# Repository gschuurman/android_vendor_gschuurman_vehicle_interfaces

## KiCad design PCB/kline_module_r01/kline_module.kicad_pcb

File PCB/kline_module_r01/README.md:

# K-line module rev 0.1 (MG F, MEMS 1.9) - 2026-11-15

A small 2-layer board that stacks on main board rev 0.6 socket **J10**, like the other modules, and connects the
RP2350B UART to the car's K-line through Glenn's ST **L9637D**.

- Size **28.5 x 20.5 mm**, 1.6 mm, 2 layers, GND pour on both sides. Well inside the JLCPCB 100 x 100 mm promo.
- Status: fully routed, **0 unconnected, 0 copper/clearance errors**. `drc.rpt` only lists the KiCad standard library
  names (not installed in the build container) and one silkscreen nick at a corner.
- All parts are 0805 or larger (SOT-23, SOD-123, SMA, SO-8, 2512), all on the top side. Only the 2x4 header sits underneath.
- Files: `kline_module.kicad_pro/.kicad_pcb/.kicad_sch` (made in KiCad 7, open in KiCad 10), `kline_module_gerbers.zip`
  (upload to JLCPCB), `kline_module_bom.csv`, `kline_module_lcsc_order.csv` (LCSC numbers and quantity per board),
  `kline_module_schematic.pdf`, renders in `render/`, generator scripts in `scripts/` (placement and netlist in `design.py`).

## Fit on the main board (rev 0.6)

The board is drawn in main-board coordinates, so it can be checked directly against `carradio_peripheral_rev06.kicad_pcb`.

| What | Main board | Module |
|---|---|---|
| J10 (2x4 socket, 8.5 mm) | pin 1 at (78.19, 27.63) | J1 2x4 male header on the underside, pin 1 at (78.19, 27.63); all 8 pins checked in the script |
| H8 (M2) | (69.6, 18.5) | H1 2.2 mm hole at (69.6, 18.5), copper keep-out 5.2 mm |
| outline | free zone above J10 | x 65.0-93.5, y 11.5-32.0 (audio module ends at x 63.5, USB module starts at y 32.5) |

Under the module there are only low SMD parts, the J10 socket, F6 and the HDMI pairs. The module edge reaches
0.5 mm over the back of the HDMI socket J13 (courtyard to y 12.0), which is about 6 mm tall, so there is ~5 mm of air
at the 11 mm stack height. It stays clear of the FPC J14 (starts at x 94.2); unplug the module to open the J14 latch.
Screw: M2 x 18 through the module, the printed 11 mm M2 sleeve (`module_spacers`) and the main board into the H8 insert.

J1 is two 1x4 male headers (Ckmtw B-2100S04P-A110, same family as earlier boards), one per row. Plug them into J10
first, put the module on top and solder them from above, so they line up.

## Circuit

| J1 pin | Main board net | Use |
|---|---|---|
| 1 | +3V3_MCU | U1 VCC |
| 2, 6 | GND | |
| 3 | EXP_GP32 (UART0 TX) | U1 TX |
| 4 | EXP_GP33 (UART0 RX) | U1 RX |
| 5 | EXP_GP28 | K-line power enable (high = on) |
| 7 | VBAT_KLINE (via F6, after D1 reverse diode and SMBJ22A) | Q1 source |
| 8 | +5V_AON | not used |

- **U1 L9637D**: VCC from 3.3 V is inside the datasheet range (3-7 V). RX then swings 0-3.3 V straight into GPIO33,
  and TX accepts 3.3 V logic (VIH max 2.5 V). TX, RX and LO have internal pull-ups to VCC, so nothing else is needed.
  VS max 36 V; the main-board TVS clamps at 35.5 V.
- **Q1 FDN5618P** (same as main-board Q2) with D1 12 V zener, R2 100k and Q2 2N7002 + R3: switches battery to VS and to the
  pull-up. GPIO28 low (also the default through R4 10k) = off. That gives zero parked drain and, more importantly,
  no 12 V pushed through 510 ohm into the ECU's K-line while the ECU is unpowered.
- **R1 510 ohm 2512** (1 W, 0.4 W worst case with K stuck low): the ISO 9141 tester pull-up. **JP1** is a bridged solder jumper;
  cut it if you want to run without the module's pull-up.
- **D2 SMAJ26CA** bidirectional TVS and **C4 1 nF** on K (ISO 9141 allows up to 1.3 nF; 470 pF also fine).
- **D3** green LED: lit while the K-line side is powered.
- L-line is not used by the MEMS 1.9: LI and LO stay open (the datasheet defines LO for an open LI).

## Car side

**J2 = JST S2B-XH-A side entry** (2.5 mm XH, crimp housing XHP-2), pin 1 **K-line**, pin 2 **GND**. The opening faces
the back plate (main-board x = 100). Glenn's harness already uses XH for the VIM3 power, so the same crimps work.
- Forum sources (not a wiring diagram) say the MEMS 1.9 K-line is OBD-II socket pin 7 (ECU red connector pin 31 on at
  least one car), GND pins 4/5. Check this on your car before wiring.
- Space: the plug and wire leave the module edge at x 93.3; the back plate inner face is at about x 101. That is
  tight for a bend; a small hole/grommet in the back plate lets the wire run straight out.

## Firmware notes (not written yet)

- GPIO28 high, wait ~10 ms, then talk.
- MEMS 1.9 (per rovermems.com): ISO 9141 5-baud init with ECU address 0x16, bit-banged on GPIO32 as SIO, then UART0
  **9600 8N1** half duplex (you read back your own echo on GPIO33).
- GPIO28 low when ACC goes off.

## Order

JLCPCB: upload `kline_module_gerbers.zip`, defaults (2 layers, 1.6 mm, HASL, 5 pcs), no assembly.

Parts (checked against the rev 0.6 order of 2026-10-04, `pcb/ordering/lcsc_final_cart.csv` + `mouser_final_import.csv`,
assuming one set built with at most 2 spares used):

| Ref | Part | Source |
|---|---|---|
| U1 | L9637D | Glenn's own |
| J2 | JST XH 2-pin right angle | Glenn's own; cable needs an XHP-2 housing + 2 SXH crimps |
| Q1 | FDN5618P | rev 0.6 leftover (5 ordered, 1 used) |
| D1 | BZT52C12 | leftover (10 ordered, 2 used) |
| Q2 | 2N7002 | leftover (50 ordered) |
| D3 | KT-0805G LED | leftover (50 ordered) |
| R5 | 4.7k 0805 | leftover (100 ordered) |
| C1, C2 | 100 nF | leftover 0603 C14663 (150 ordered, ~48 used); fits the 0805 pads |
| R3, R4 | 10k | leftover 0603 C98220 (40 ordered, ~18 used) |
| R2 | 100k | leftover 0603 C25803 (100 ordered) |
| C4 | 1 nF | leftover 0603 C1588 (6 ordered, 1 used) |
| J1 | 2x 1x4 header | leftover C124378 (10 ordered, 1 used) |
| **R1** | **510R 2512 1W** | **buy: LCSC C269361** |
| **D2** | **SMAJ26CA** | **buy: LCSC C571371** |

`kline_module_lcsc_order.csv` holds only the two parts to buy; `kline_module_bom.csv` is the full BOM.

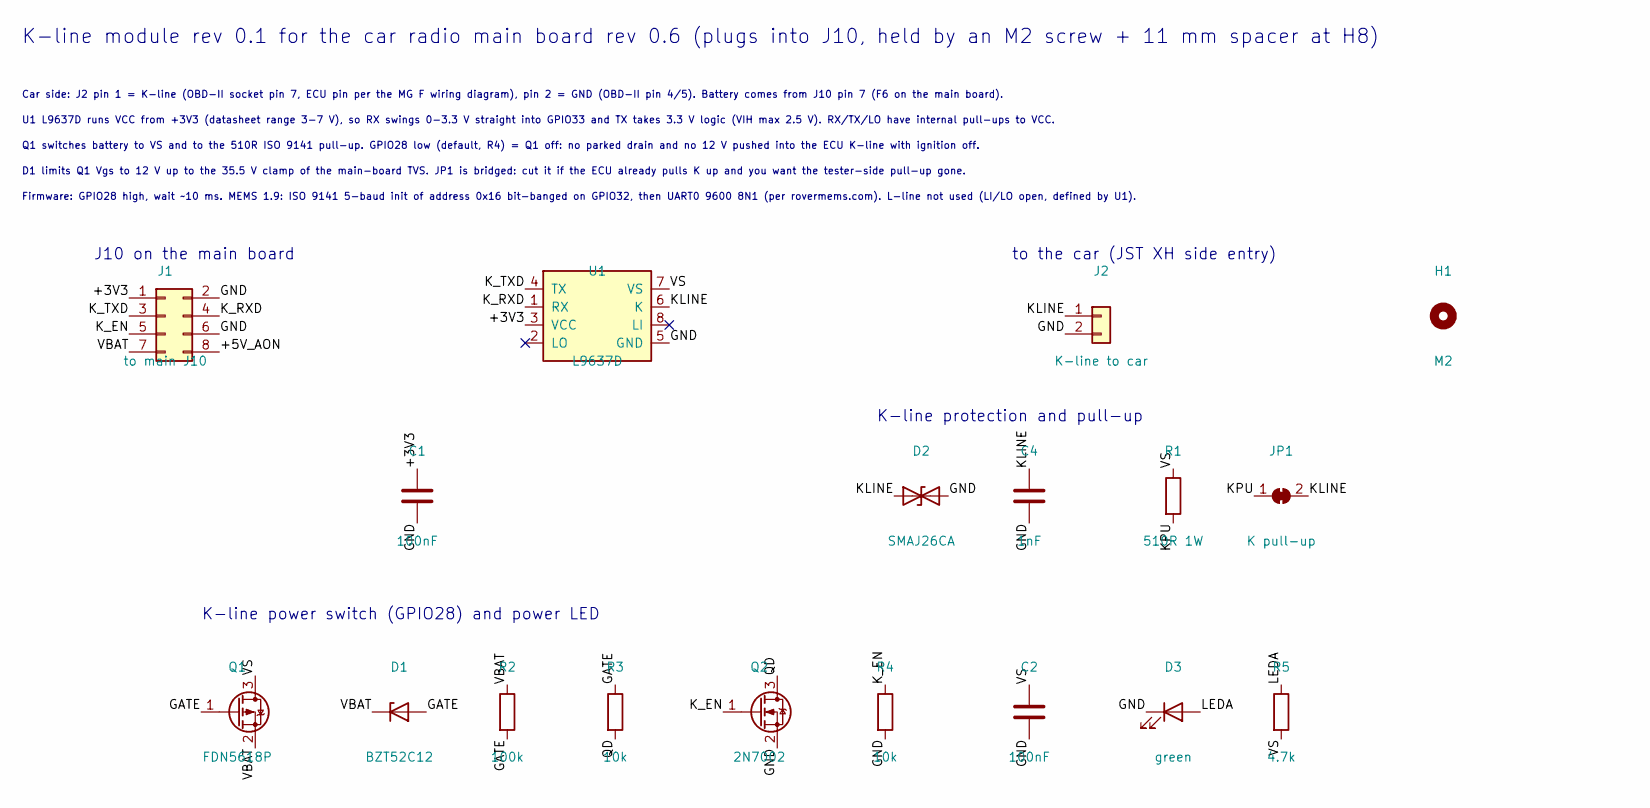
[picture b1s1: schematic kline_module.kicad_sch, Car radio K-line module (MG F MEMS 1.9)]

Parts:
C1, C2: 100nF; C_0805_2012Metric_Pad1.18x1.45mm_HandSolder; LCSC C49678
C4: 1nF; C_0805_2012Metric_Pad1.18x1.45mm_HandSolder; LCSC C1588
D1: BZT52C12; D_SOD-123; LCSC C124196
D2: SMAJ26CA; D_SMA; LCSC C571371
D3: green; LED_0805_2012Metric_Pad1.15x1.40mm_HandSolder; LCSC C2297
H1: M2; MountingHole_2.2mm_M2
J1: to main J10; PinHeader_2x04_P2.54mm_Vertical; LCSC C124378
J2: K-line to car; JST_XH_S2B-XH-A_1x02_P2.50mm_Horizontal; LCSC C157931
JP1: K pull-up; SolderJumper-2_P1.3mm_Bridged_RoundedPad1.0x1.5mm
Q1: FDN5618P; SOT-23; LCSC C400792
Q2: 2N7002; SOT-23; LCSC C8545
R1: 510R 1W; R_2512_6332Metric_Pad1.40x3.35mm_HandSolder; LCSC C269361
R2: 100k; R_0805_2012Metric_Pad1.20x1.40mm_HandSolder; LCSC C149504
R3, R4: 10k; R_0805_2012Metric_Pad1.20x1.40mm_HandSolder; LCSC C17414
R5: 4.7k; R_0805_2012Metric_Pad1.20x1.40mm_HandSolder; LCSC C17673
U1: L9637D; SOIC-8_3.9x4.9mm_P1.27mm; LCSC C153038

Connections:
+3V3: C1.1, J1.1, U1.3 (VCC)
+5V_AON: J1.8
GATE: D1.2 (A), Q1.1 (G), R2.2, R3.1
GND: C1.2, C2.2, C4.2, D2.2 (A2), D3.1 (K), J1.2, J1.6, J2.2, Q2.2 (S), R4.2, U1.5 (GND)
KLINE: C4.1, D2.1 (A1), J2.1, JP1.2 (B), U1.6 (K)
KPU: JP1.1 (A), R1.2
K_EN: J1.5, Q2.1 (G), R4.1
K_RXD: J1.4, U1.1 (RX)
K_TXD: J1.3, U1.4 (TX)
LEDA: D3.2 (A), R5.1
QD: Q2.3 (D), R3.2
VBAT: D1.1 (K), J1.7, Q1.2 (S), R2.1
VS: C2.1, Q1.3 (D), R1.1, R5.2, U1.7 (VS)

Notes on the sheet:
K-line module rev 0.1 for the car radio main board rev 0.6 (plugs into J10, held by an M2 screw + 11 mm spacer at H8)
Car side: J2 pin 1 = K-line (OBD-II socket pin 7, ECU pin per the MG F wiring diagram), pin 2 = GND (OBD-II pin 4/5). Battery comes from J10 pin 7 (F6 on the main board).
U1 L9637D runs VCC from +3V3 (datasheet range 3-7 V), so RX swings 0-3.3 V straight into GPIO33 and TX takes 3.3 V logic (VIH max 2.5 V). RX/TX/LO have internal pull-ups to VCC.
Q1 switches battery to VS and to the 510R ISO 9141 pull-up. GPIO28 low (default, R4) = Q1 off: no parked drain and no 12 V pushed into the ECU K-line with ignition off.
D1 limits Q1 Vgs to 12 V up to the 35.5 V clamp of the main-board TVS. JP1 is bridged: cut it if the ECU already pulls K up and you want the tester-side pull-up gone.
Firmware: GPIO28 high, wait ~10 ms. MEMS 1.9: ISO 9141 5-baud init of address 0x16 bit-banged on GPIO32, then UART0 9600 8N1 (per rovermems.com). L-line not used (LI/LO open, defined by U1).
J10 on the main board
to the car (JST XH side entry)
K-line protection and pull-up
K-line power switch (GPIO28) and power LED

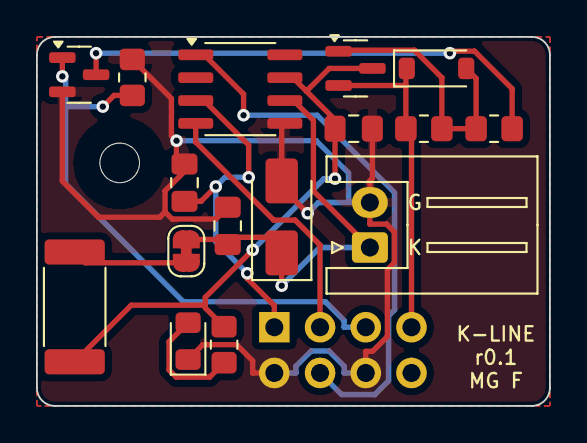
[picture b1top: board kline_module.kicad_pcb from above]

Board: 2 copper layers, 28.5 x 20.5 mm, 18 parts (1 on the bottom side), 12 nets.

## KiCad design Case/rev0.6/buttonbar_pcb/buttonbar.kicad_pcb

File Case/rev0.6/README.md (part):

# 1 DIN case for peripheral board rev 0.6 + VIM3/M2X

`car_radio_rev06_case.scad` is a rework of the prototype case (`car_radio improved_0.2.scad`). It keeps the same parts and style: heat-set inserts, DIN clip pockets, removal-key slots, the front plate with the screen tray and flanged spacers, separate side, top and bottom panels, and a back plate. Pick a part with `part_to_print`. `show_boards` draws ghost boards, plugs and jacks in the assembly view, and `show_lid = false` lets you look inside. The OpenSCAD console prints the fit checks.

Rendered and exported with OpenSCAD 2021.01. Every part exports as a clean, simple (manifold) STL: see `stl/` for the files and `render/` for the pictures.

## Layout

- **Main board** (rev 0.6, 100 x 100 mm). The outline, the mounting holes and every connector position come from `PCB/rev0.6/main/carradio_peripheral_rev06.kicad_pcb`. The modules come from `rev0.6/usb` and `rev0.4/gnss|audio`. The board sits rear right on **eight 12.6 mm posts, one under every hole** (8 mm before the VIM3/M2X rework, see below), each with a heat-set insert (see the next section). It is **turned 90 degrees** so that its KiCad right edge (x = 100) faces the back plate:
  - The three USB-A sockets on the USB module face the rear: J17 RTL-SDR, then J19 and J20 for external devices. In assembly coordinates they sit at X = 23.1, 41.3 and 59.5 mm, with their centre about 27.8 mm above the case bottom.
  - The KiCad top edge, with J2 IDC, J13 HDMI, J18 VIN and J5 power key, faces the VIM3 on the left. The ISO and button connectors (J1, J8, J12, J7) are on the right-hand side. All of these are vertical apart from J13.
- **VIM3 + New M2X** sits front left in a pocket in the bottom panel, ports facing the main board, 40-pin header against the left side, held by a screwed retainer strip at the front and a tongue on the back plate at the rear. See "VIM3 / M2X mount" below.
- **HDMI bay**: J13 faces left, so the HDMI plug goes in from the left, behind the VIM3 stack. That is the reason the case is **134 mm deep inside, 146 mm overall** (the prototype was 110 / 118). That is still within a normal DIN cage, but check behind your dash.
- **Back plate**: SMA bulkhead (GPS, with an anti-rotation flat, right next to the SDR port at USB height), 3.5 mm panel jack (MIC, M6 thread), RCA (CAM), three USB-A openings, and one cable slit (8 x 16 mm, as on the prototype) for the ISO A + C1 pigtails. The pigtails carry the 12 V power, so they are the "power" opening. The slit is open to the top edge, so you can lay the loom in before fitting the lid. The USB openings have a shared outside pocket that leaves only 1 mm of plate, so plug overmolds can seat fully. The old audio-jack and SPDIF cutouts are gone. The labels are engraved and mirrored so they read correctly from behind.
- Vent slots in the lid and the bottom panel over and under the VIM3. There is now a third assembly screw per side, because the case is deeper. The release-key holes and the serial pogo plug are disabled (`add_key_slots`, `add_uart_pogo`).

## Main-board holes and module standoffs

I checked the holes against two independent sources: the KiCad footprints and the Gerber drill file (`fab/main/...-PTH.drl`). The two agree exactly. There are 8 mounting holes. The only other large hole is the 3.81 mm NPTH, which is the F4 fuse-holder peg, not a mounting hole. For each module, I matched its header pins to the main-board socket (all pins within 0.000 mm) and then mapped the module's own mounting hole across. All three land exactly on a main-board hole.

| Hole | KiCad (x, y) | Drill | Used by | Post in the case (assembly X, Y) | Insert bore | Hardware |
|---|---|---|---|---|---|---|
| H1 | 4.5, 4.5 | 3.2 | main board | -14.5, 42.5 | 4.2 x 6 | M3 x 8 screw |
| H2 | 95.5, 4.5 | 3.2 | main board | -14.5, 133.5 | 4.2 x 6 | M3 x 8 screw |
| H3 | 4.5, 95.5 | 3.2 | main board | 76.5, 42.5 | 4.2 x 6 | M3 x 8 screw |
| H4 | 95.5, 95.5 | 3.2 | main board | 76.5, 133.5 | 4.2 x 6 | M3 x 8 screw |
| H5 | 67.8, 83.7 | 2.7 | USB module (its H1 at 3.8, 51.2) | 64.7, 105.8 | 3.6 x 5 | M2.5 x 11 M-F standoff + M2.5 screw |
| H6 | 31.0, 16.5 | 2.7 | audio module rev 0.4/0.7 (its hole at 37.5, 4.0, turned 270 deg) | -2.5, 69.0 | 3.6 x 5 | M2.5 x 11 M-F standoff + M2.5 screw |
| H7 | 3.2, 34.3 | 2.7 | GNSS module (its hole at 3.2, 15.3) | 15.3, 41.2 | 3.6 x 5 | M2.5 x 11 M-F standoff + M2.5 screw |
| H8 | 69.6, 18.5 | 2.2 | future K-line module on J10 | -0.5, 107.6 | 3.2 x 4 | M2 x 11 M-F standoff + M2 screw |

- The M3 pattern is 91.0 x 91.0 mm. I measured it again from the exported `bottom.stl` and got the same 91.0 x 91.0, with every post at the position in the table.
- 11 mm = 8.5 mm socket + 2.5 mm header body, so a module sits flat on its standoff. The standoff's male thread passes through the 1.6 mm main board into the insert. Use a male thread of at least 4 mm (M2.5) or 3 mm (M2).
- You melt each insert in from the top of its post before the board goes in. A screw-clearance bore continues below every insert, so long screws don't bottom out. It stops 0.6 mm above the underside of the panel, so nothing shows from below.
- No bottom-side pad comes within the post footprints. The nearest one is 6.2 mm from a hole centre (J21 pin 10 at H5), and the largest post radius is 4 mm. The posts sit on the holes' own plated rings.
- Insert sizes are parameters in `mb_mounts` (bore, depth, lead-in, post OD, screw clearance). M3 and M2 are the same as your prototype. **M2.5 (3.6 mm bore) is new, so check it against your inserts.**
- The posts don't cover the stacked capture board (rev 0.7). It screws to the USB module, not to the main board.

## Side-panel inserts

The side wall plus ledge is only 7 mm thick. A 4.2 mm M3 insert bore centred in it broke through the ledge face, so it had almost no material to grip. Every side-panel insert now sits in its own **boss**: a 9 mm round pad around the insert axis, blended into the wall, reaching 2.5 mm past the ledge face. That leaves at least 2.1 mm of wall inside and 2.9 mm to the outer face.

- Six vertical bosses per side (top and bottom, at Y 20, 67 and 119) for the lid and bottom-panel screws.
- Two front bosses per side, 11 mm long, for the front plate. These four screws carry the front plate with the display.
- Two rear bosses per side, 9 mm long, for the back plate.
- **Changed:** the lower rear insert moved from z 12 to z 20 (`rear_mount_z`), because at z 12 its boss would hit the corner of the main board. The back-plate holes moved with it. The front holes stay at z 12 / 37.5.
- **Changed (2026-11-05):** the VIM3 sits 0.8 mm from the left ledge (`vim3_side_clear`); the left side's lower insert pads are notched where the M2X edge passes, and the right side has no lower rear insert (`right_drop_low_rear`).
- Checked in OpenSCAD: the side panels have 0 mm³ of overlap with the boards, plugs, jacks, bottom panel, back plate and front plate.
- Sizes are parameters: `side_boss_d`, `side_boss_extra`, `front_boss_length`, `rear_boss_length`. The bore is unchanged (4.2 mm, 6.2 deep).

## Things to know before printing

1. **Screen ribbon (conflict).** With the USB ports at the rear, J14 (the display FPC) also faces the rear, and its ribbon leaves the board edge towards the back plate. The panel's own FPC cannot reach it. You need a 40-pin 0.5 mm FFC extension of about 160 mm plus an FPC joiner board near the front. The ribbon wraps round the board edge at J14 and runs forward **under** the main board (that is why the posts are 8 mm). The back plate has a 2 mm relief on the inside behind J14 for the wrap. Now that every hole has a post, H6 and H8 sit right behind J14, so the ribbon can't run straight forward. It needs a 45 degree fold just behind H8 into the post-free lane at X 20-42 (between H7 and H5), then a fold in front of the board over to the front slot (X = -12). The orange ghost in the assembly shows this route, set by `ffc_lane_x`, `ffc_turn_y` and `ffc_front_y`. Because of the wrap, check whether you need a same-side or an opposite-side contact FFC. Moving the USB-A ports to the other edge in the next revision removes all of this.
2. **The RTL-SDR dongle plugs in from outside** the back plate, because J17 is one of the rear sockets. The dongle sticks out the back, which is also where the FM/DAB antenna connects. If there is not enough room behind the cage, use a short USB extension.
3. **HDMI cable.** FPV ribbon with 90 degree "A2" heads (ribbon up). See "VIM3 / M2X mount" below.
4. **VIM3 / M2X numbers** now come from the Khadas DXF/STEP files and Glenn's measurements; see "VIM3 / M2X mount" below.
5. **USB-A height**: `usb_a_center_above_module = 2.6` assumes the Molex 67643 shell sits flat on the module. Check it on your stacked board. The openings are 15 x 8 mm, so they allow about +/-1 mm.
6. **Jack holes**: SMA 6.6 mm, mic 6.2 mm (PJ-392), RCA 10 mm (as on the prototype). The plate is 3 mm thick.

## OpenSCAD in the cloud environment

Cloud sessions start from a fresh container, so a manual install is lost when the session ends. To have OpenSCAD in every new session of this project, add this to the cloud environment's **Setup script** (Project settings, Cloud environment, gear icon):

```
apt-get update && apt-get install -y --no-install-recommends openscad xvfb xauth
```

xvfb is needed for PNG renders (`xvfb-run -a openscad -o view.png ...`). STL export works without it:

```
openscad -o bottom.stl -D 'part_to_print="bottom"' car_radio_rev06_case.scad
```

## Screen tray and button bar (v2, 2026-11-04)

Replaces the 18 mm task bar and the screen-off tab, which were too big.

- **Front is 179.5 x 122.5 mm**: the screen tray is 109.5 mm and the button bar 13 mm. The previous version was 140.5 mm tall. There is no button on the top edge.
- **Screen tray (`screen_tray`)** is one piece. The screen is taped in as before, with the pocket 1.5 mm larger and turned 180 deg. The bottom corners are square so the bar continues the outline. Four M2 inserts in the back of the base take the bar.
- **Button bar (`button_bar`)** is the only separate front part. It has a tongue that lies behind the tray and is screwed on from the back with 4x M2x6 into the tray inserts. No screws show at the front. Print it with its back face down; the front skin is then the top surface, which you can iron.
- **9 buttons in one line** (left = driver side): home | vol-, mute, vol+ | screen off (middle) | previous, play/pause, next | voice.
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
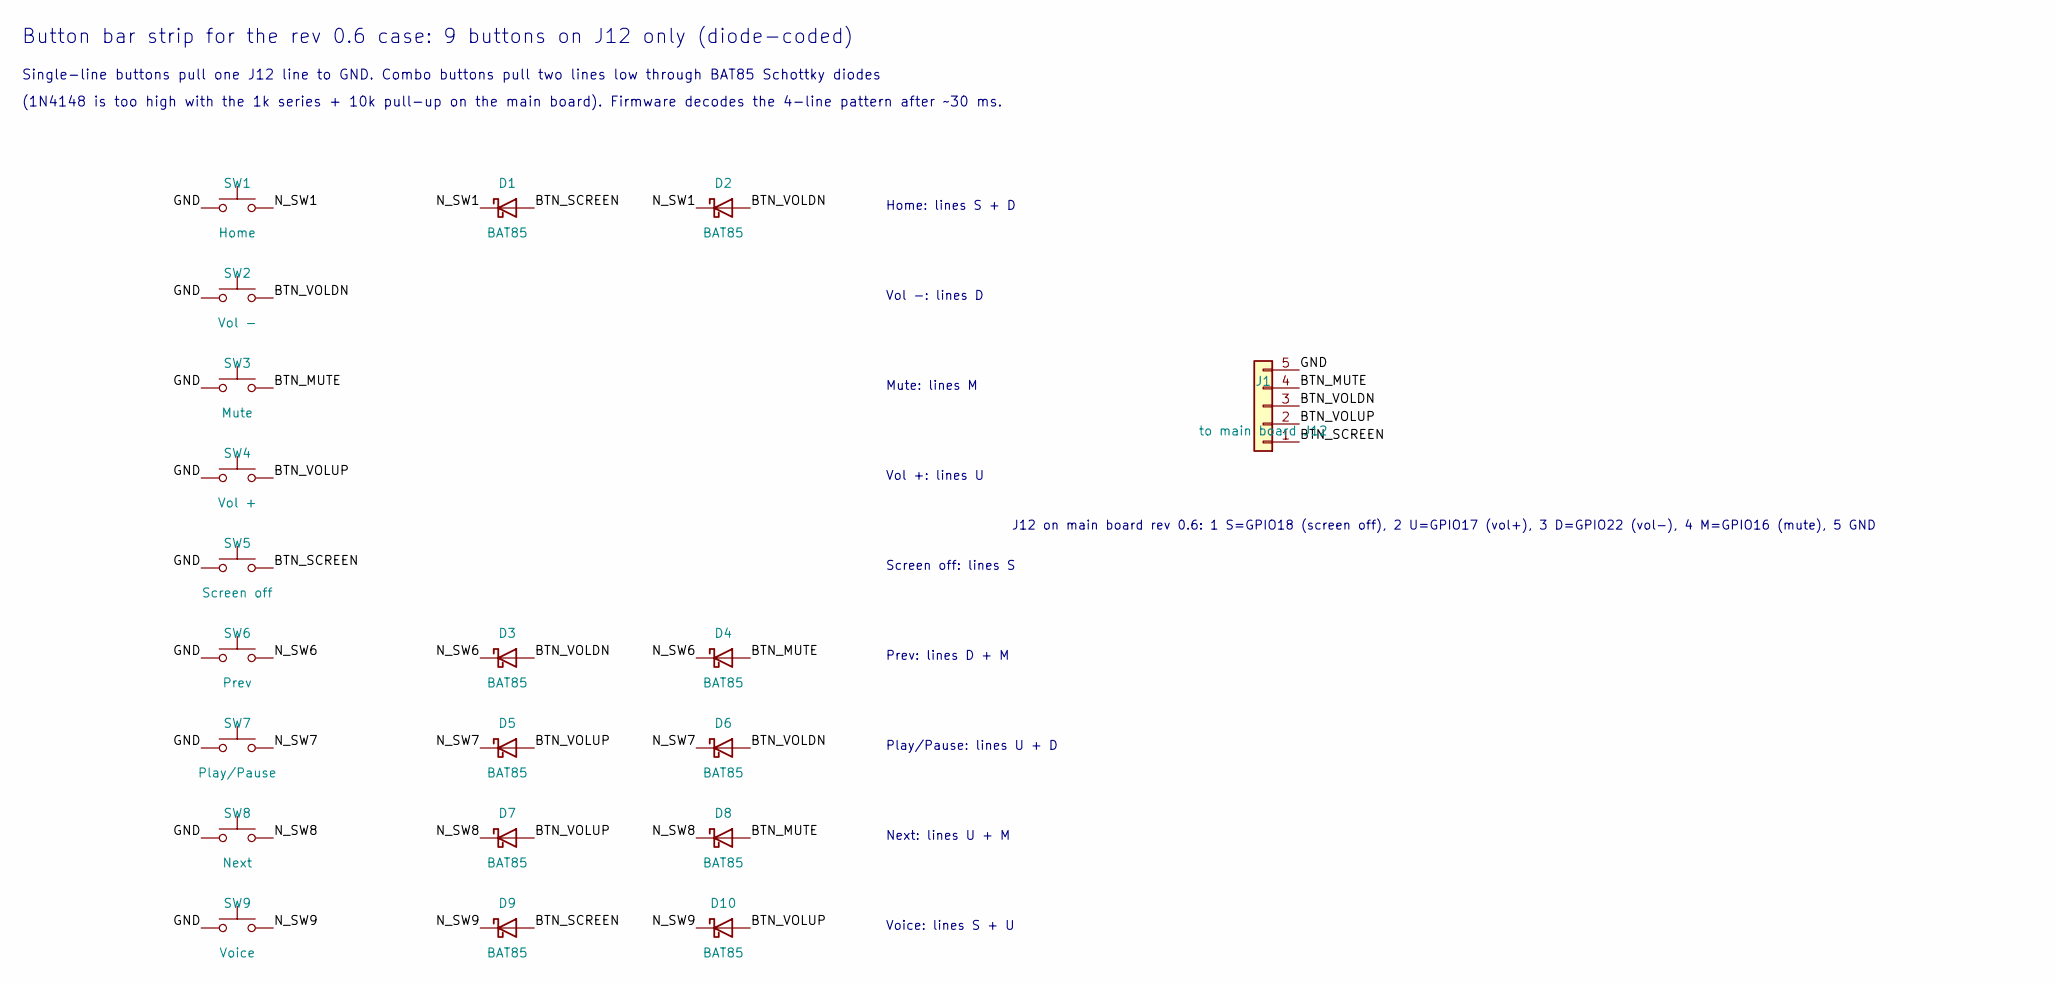
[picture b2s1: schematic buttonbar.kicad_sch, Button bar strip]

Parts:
D1, D2, D3, D4, D5, D6, D7, D8, D9, D10: BAT85; D_DO-34_SOD68_P7.62mm_Horizontal
J1: to main board J12; PinHeader_1x05_P2.54mm_Vertical
SW1: Home; SW_Tactile_6x3.5mm_2pin_P5.08mm
SW2: Vol -; SW_Tactile_6x3.5mm_2pin_P5.08mm
SW3: Mute; SW_Tactile_6x3.5mm_2pin_P5.08mm
SW4: Vol +; SW_Tactile_6x3.5mm_2pin_P5.08mm
SW5: Screen off; SW_Tactile_6x3.5mm_2pin_P5.08mm
SW6: Prev; SW_Tactile_6x3.5mm_2pin_P5.08mm
SW7: Play/Pause; SW_Tactile_6x3.5mm_2pin_P5.08mm
SW8: Next; SW_Tactile_6x3.5mm_2pin_P5.08mm
SW9: Voice; SW_Tactile_6x3.5mm_2pin_P5.08mm

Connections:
/BTN_MUTE: D4.2 (A), D8.2 (A), J1.4, SW3.2
/BTN_SCREEN: D1.2 (A), D9.2 (A), J1.1, SW5.2
/BTN_VOLDN: D2.2 (A), D3.2 (A), D6.2 (A), J1.3, SW2.2
/BTN_VOLUP: D5.2 (A), D7.2 (A), D10.2 (A), J1.2, SW4.2
/N_SW1: D1.1 (K), D2.1 (K), SW1.2
/N_SW6: D3.1 (K), D4.1 (K), SW6.2
/N_SW7: D5.1 (K), D6.1 (K), SW7.2
/N_SW8: D7.1 (K), D8.1 (K), SW8.2
/N_SW9: D9.1 (K), D10.1 (K), SW9.2
GND: J1.5, SW1.1, SW2.1, SW3.1, SW4.1, SW5.1, SW6.1, SW7.1, SW8.1, SW9.1

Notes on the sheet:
Button bar strip for the rev 0.6 case: 9 buttons on J12 only (diode-coded)
Single-line buttons pull one J12 line to GND. Combo buttons pull two lines low through BAT85 Schottky diodes
(1N4148 is too high with the 1k series + 10k pull-up on the main board). Firmware decodes the 4-line pattern after ~30 ms.
Home: lines S + D
Vol -: lines D
Mute: lines M
Vol +: lines U
Screen off: lines S
Prev: lines D + M
Play/Pause: lines U + D
Next: lines U + M
Voice: lines S + U
J12 on main board rev 0.6: 1 S=GPIO18 (screen off), 2 U=GPIO17 (vol+), 3 D=GPIO22 (vol-), 4 M=GPIO16 (mute), 5 GND

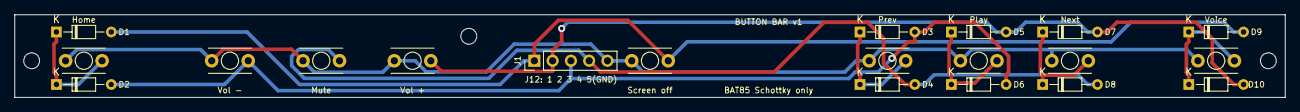
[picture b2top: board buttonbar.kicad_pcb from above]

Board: 2 copper layers, 176.7 x 11.5 mm, 23 parts (0 on the bottom side), 10 nets.

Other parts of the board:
H1, H2, H3: M2 hole; MountingHole_2.2mm_M2

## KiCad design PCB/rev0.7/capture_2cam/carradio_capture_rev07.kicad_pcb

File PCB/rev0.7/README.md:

# PCB rev 0.7: two-camera capture

Rev 0.7 only changes the USB module and adds a capture module, in two versions: `capture_1cam/` (one camera)
and `capture_2cam/` (two cameras). Both plug into the same J29 socket on the USB module; build one of them. The main, audio and
GNSS boards stay at rev 0.6.

## Two-camera capture module (`capture_2cam/`)

Two MacroSilicon MS2107 (LCSC C42374499, LQFP-48), one per camera: analog CVBS in, USB 2.0 UVC out,
behind a CH334R 4-port hub (U10, C4154405) so both share the USB module's single J29 port. Android sees two
normal external cameras (default VID:PID 534d:0021 each), so no driver is needed. The RearViewCamera app
currently opens the first external camera; it needs a setting (or a USB-path match) to pick the reverse one.

- 36 x 67.5 mm, 2 layers. Same outline and H1 as the USB module, extended 12.5 mm downward to the main board's
  bottom edge (the USB module's right edge is already the main board edge).
- J1 (CAM1) and J101 (CAM2): JST PH 2-pin video in (1 = CVBS, 2 = GND), each with 75 ohm termination, 47 nF
  coupling and a USBLC6 ESD clamp.
- J2: 2x3 2.54 mm male header on the bottom side, plugs into USB module J29 and feeds the hub upstream.
- Hub port 1 camera 1, port 2 camera 2, port 3 to J3 (1x4 pads, not fitted: 5 V, D-, D+, GND) for an
  optional third capture board or a test device, port 4 unused.
- Each channel: 12 MHz crystal, internal LDOs, status LED (D1/D101). EEPROMs U3/U103 and R5/R105 are DNP and
  sit on the underside; fit one only to give a camera its own USB name/IDs (ms-tools).
- Routed, DRC 0 unconnected, no copper errors (silkscreen warnings only; H1 is a board-only part).
- Each camera's own 12 V still comes from the reverse-lamp (or other) feed, not from this board.

### How many cameras

Each MS2107 sends uncompressed YUV, about 21 MB/s per PAL/NTSC camera. Everything shares the VIM3 header's
single USB 2.0 High Speed link, which can reserve about 48 MB/s for video, so two cameras can stream at once
(about 41 MB/s) with the RTL-SDR (about 5 MB/s, bulk) still fitting. A third camera on J3 only works if it does
not stream at the same time as the other two. These are calculated numbers, not measured.

### USB pair lengths (mm)

| Pair | D+ | D- |
|---|---|---|
| J2 to hub (upstream; D+ hand-routed on B.Cu between the J2 GND pins) | 12.6 | 10.4 |
| hub to camera 1 | 33.1 | 32.3 |
| hub to camera 2 | 57.1 | 64.8 |
| hub to J3 (not fitted) | 33.2 | 39.0 |

On the USB module D+ is already about 12.7 mm longer than D- (hub 2 to J29), so the upstream skew is about
15 mm in total. Fine for USB 2.0 High Speed in practice; a meander would tidy it if wanted.

## Single-camera capture module (`capture_1cam/`)

The first rev 0.7 board: one MS2107 wired straight to J2, no hub. 36 x 55 mm, the USB module's exact outline.
Same input circuit (J1 JST PH, 75 ohm, 47 nF, USBLC6), optional EEPROM U3/R5 (DNP) on the top side, status
LED D1. Routed, DRC 0 unconnected, no copper errors. USB pair J2 to MS2107: D+ 14.0 mm, D- 10.7 mm; with the
USB module that is about 16 mm of skew in total. Draws about 0.2 A; the 1.1 A F7 covers it too.

## USB module change (`usb/`)

- J29 2x3 female socket (CJT A2541HWV-2x3P, C239343, 8.5 mm body): 1/2 +5V_CAP, 3 D+, 4 D-, 5/6 GND. Wired
  to hub 2 (U14 CH334R) port 4, which was unused. Hub 2 is now full (two phone ports, SDR, capture).
- F7 1.1 A PTC (Bourns MF-NSMF110-2, C89654) feeds +5V_CAP from +5V_SYS, so the capture board only has power
  while the VIM3 is on. Load: hub + two MS2107, about 0.5 A.
- One B.Cu GND track near J29 removed; GND still reaches everything via the pours.
- DRC 0 unconnected, no copper errors. All rev 0.6 symbol UUIDs unchanged.

## Stack

The capture board sits about 11 mm above the USB module (8.5 mm socket + 2.5 mm header spacer), clear of the
USB-A sockets. Use an M2.5 x 11 standoff at H1 on top of the USB module's H1 standoff. Check the USB-A socket
height on the real parts before ordering. The extra 12.5 mm overhangs the main board's bottom strip above the
display-button (J12) and light-sensor (J7) plugs, about 22 mm up; leave room for their wires to bend.

## Regenerating

- `layout/capture_gen_1cam.py` / `capture_gen_2cam.py` write the capture schematics and BOMs (2cam: one `channel(k)`
  per camera, nets CAMk_*, refs +100 for camera 2). Run them inside the matching folder.
- `layout/gen7.py usb` writes the USB module schematic (new parts appended at the end
  so rev 0.6 UUIDs stay put).
- `layout/usb07.py` / `usb07_post.py` and `capture_pcb_1cam.py` / `capture_pcb_2cam.py` / `capture_post.py` do
  placement and post-Freerouting cleanup (KiCad 10 pcbnew Python).

## Bring-up wizards

Step-by-step bench wizards (multimeter first, then first power): `usb/WIZARD.html`, `audio/WIZARD.html`,
`capture_1cam/WIZARD.html` and `capture_2cam/WIZARD.html`. See `../wizard/README.md`.

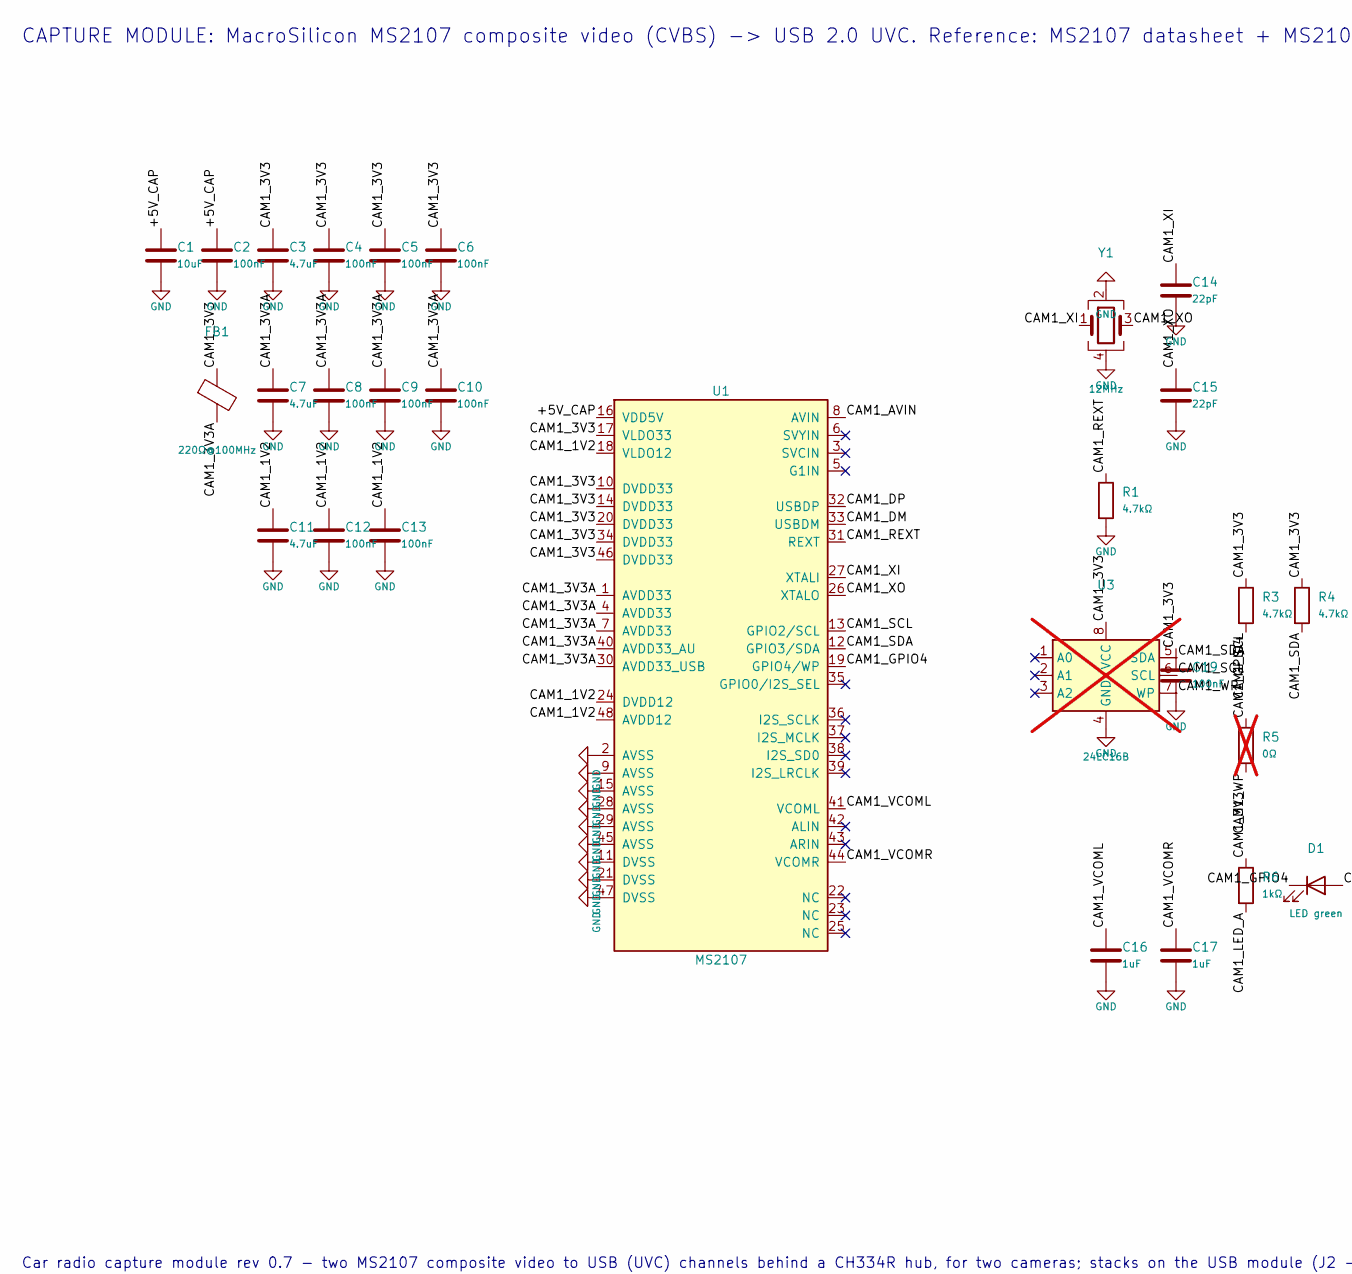
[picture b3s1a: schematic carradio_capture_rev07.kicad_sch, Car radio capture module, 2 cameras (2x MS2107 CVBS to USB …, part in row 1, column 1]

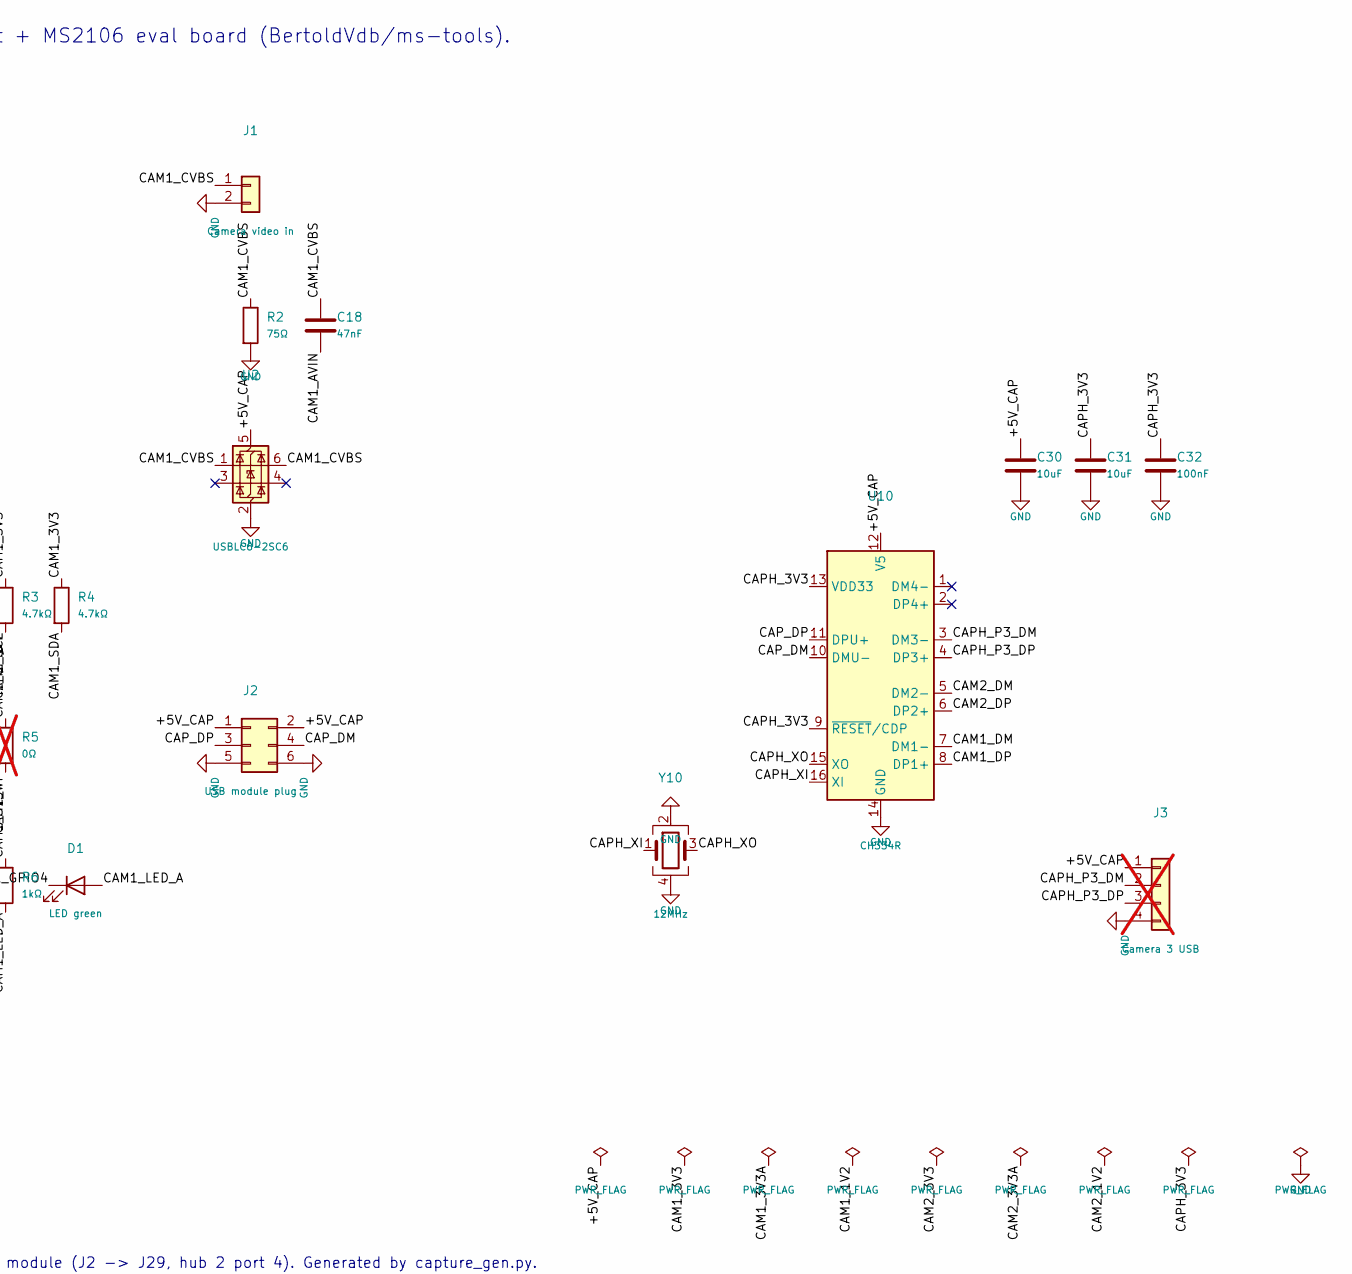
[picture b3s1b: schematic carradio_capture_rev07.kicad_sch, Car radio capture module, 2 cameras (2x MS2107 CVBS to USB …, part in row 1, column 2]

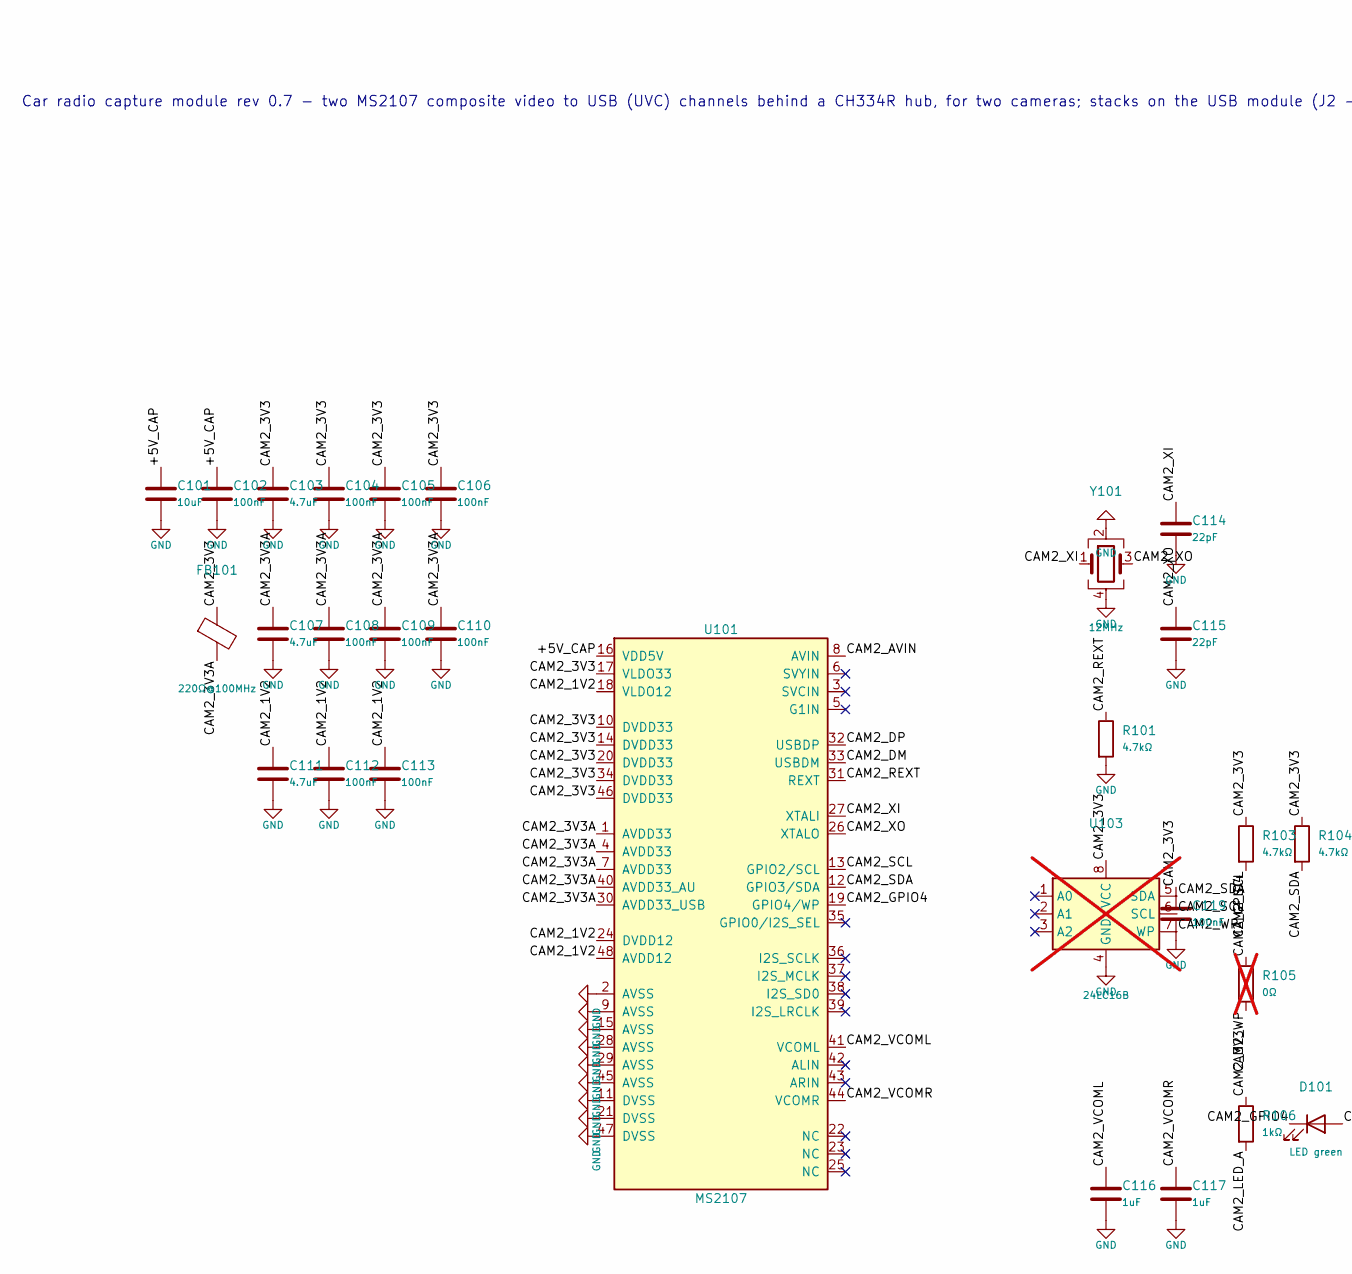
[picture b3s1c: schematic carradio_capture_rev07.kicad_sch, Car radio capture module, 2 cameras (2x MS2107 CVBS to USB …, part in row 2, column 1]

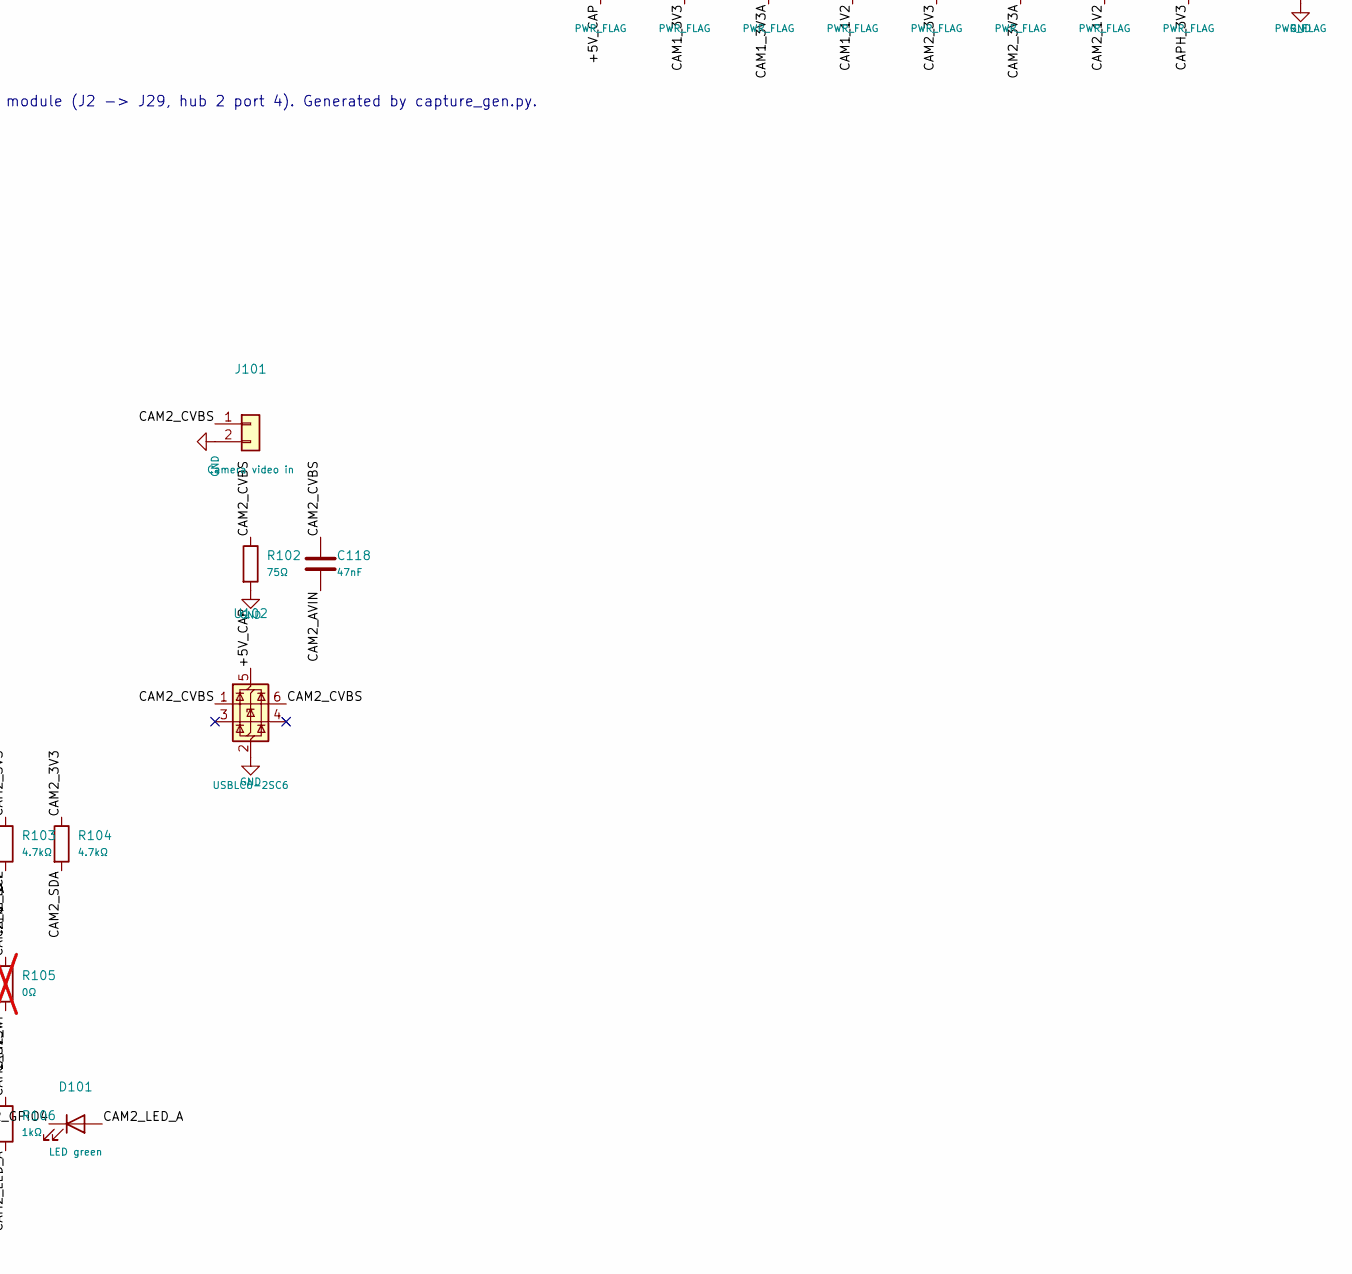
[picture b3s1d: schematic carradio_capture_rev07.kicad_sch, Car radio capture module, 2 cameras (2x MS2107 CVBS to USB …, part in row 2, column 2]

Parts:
C1, C30, C31, C101: 10uF; C_0805_2012Metric; MPN Samsung CL21A106KAYNNNE 0805 10uF 25V X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; LCSC C15850
C2, C4, C5, C6, C8, C9, C10, C12, C13, C19, C32, C102, C104, C105, C106, C108, C109, C110, C112, C113, C119: 100nF; C_0603_1608Metric; MPN YAGEO CC0603KRX7R9BB104 0603 100nF 50V 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; LCSC C14663
C3, C7, C11, C103, C107, C111: 4.7uF; C_0603_1608Metric; MPN Samsung CL10A475KO8NNNC 0603 4.7uF 16V 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; LCSC C19666
C14, C15, C114, C115: 22pF; C_0603_1608Metric; MPN 0603 22pF 50V C0G; LCSC C1653
C16, C17, C116, C117: 1uF; C_0603_1608Metric; MPN Murata GRM188R61H105KAALD 0603 1uF 50V 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; LCSC C77386
C18, C118: 47nF; C_0603_1608Metric; MPN Samsung CL10B473KB8NNNC 0603 47nF 50V X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; LCSC C1622
D1, D101: LED green; LED_0805_2012Metric; MPN KT-0805G green LED; LCSC C2297
FB1, FB101: 220Ω@100MHz; L_0603_1608Metric; MPN Murata BLM18PG221SN1D 0603 ferrite 1.4A; LCSC C80165
J1, J101: Camera video in; JST_PH_B2B-PH-K_1x02_P2.00mm_Vertical; MPN JST B2B-PH-K-S; LCSC C131337
J2: USB module plug; PinHeader_2x03_P2.54mm_Vertical; MPN XFCN PZ254V-12-6P 2x3 2.54mm male heade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; LCSC C492420
J3: Camera 3 USB; PinHeader_1x04_P2.54mm_Vertical; MPN 1x4 2.54mm header, not fitted; not fitted
R1, R3, R4, R101, R103, R104: 4.7kΩ; R_0603_1608Metric; MPN UNI-ROYAL 0603WAF4701T5E 4.7k 1%; LCSC C23162
R2, R102: 75Ω; R_0603_1608Metric; MPN UNI-ROYAL 0603WAF750JT5E 75R 1%; LCSC C4275
R5, R105: 0Ω; R_0603_1608Metric; MPN UNI-ROYAL 0603WAF0000T5E 0R; LCSC C21189; not fitted
R6, R106: 1kΩ; R_0603_1608Metric; MPN UNI-ROYAL 0603WAF1001T5E 1k 1%; LCSC C21190
U1, U101: MS2107; LQFP-48_7x7mm_P0.5mm; MPN MacroSilicon MS2107 CVBS/S-Video to USB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; LCSC C42374499
U2, U102: USBLC6-2SC6; SOT-23-6; MPN ST USBLC6-2SC6; LCSC C7519
U3, U103: 24LC16B; SOIC-8_3.9x4.9mm_P1.27mm; MPN Microchip 24LC16B-I/SN; LCSC C1349383; not fitted
U10: CH334R; QSOP-16_3.9x4.9mm_P0.635mm; MPN WCH CH334R 4-port USB 2.0 hub, QSOP-16; LCSC C4154405
Y1, Y10, Y101: 12MHz; Crystal_SMD_3225-4Pin_3.2x2.5mm; MPN YXC X322512MSB4SI 12MHz 3225; LCSC C9002

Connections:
/+5V_CAP: C1.1, C2.1, C30.1, C101.1, C102.1, J2.1, J2.2, J3.1, U1.16 (VDD5V), U2.5 (VBUS), U10.12 (V5), U101.16 (VDD5V), U102.5 (VBUS)
/CAM1_1V2: C11.1, C12.1, C13.1, U1.18 (VLDO12), U1.24 (DVDD12), U1.48 (AVDD12)
/CAM1_3V3: C3.1, C4.1, C5.1, C6.1, C19.1, FB1.1, R3.1, R4.1, R6.1, U1.10 (DVDD33), U1.14 (DVDD33), U1.17 (VLDO33), U1.20 (DVDD33), U1.34 (DVDD33), U1.46 (DVDD33), U3.8 (VCC)
/CAM1_3V3A: C7.1, C8.1, C9.1, C10.1, FB1.2, U1.1 (AVDD33), U1.4 (AVDD33), U1.7 (AVDD33), U1.30 (AVDD33_USB), U1.40 (AVDD33_AU)
/CAM1_AVIN: C18.2, U1.8 (AVIN)
/CAM1_CVBS: C18.1, J1.1, R2.1, U2.1 (I/O1), U2.6 (I/O1)
/CAM1_DM: U1.33 (USBDM), U10.7 (DM1-)
/CAM1_DP: U1.32 (USBDP), U10.8 (DP1+)
/CAM1_GPIO4: D1.1 (K), R5.1, U1.19 (GPIO4/WP)
/CAM1_LED_A: D1.2 (A), R6.2
/CAM1_REXT: R1.1, U1.31 (REXT)
/CAM1_SCL: R3.2, U1.13 (GPIO2/SCL), U3.6 (SCL)
/CAM1_SDA: R4.2, U1.12 (GPIO3/SDA), U3.5 (SDA)
/CAM1_VCOML: C16.1, U1.41 (VCOML)
/CAM1_VCOMR: C17.1, U1.44 (VCOMR)
/CAM1_WP: R5.2, U3.7 (WP)
/CAM1_XI: C14.1, U1.27 (XTALI), Y1.1
/CAM1_XO: C15.1, U1.26 (XTALO), Y1.3
/CAM2_1V2: C111.1, C112.1, C113.1, U101.18 (VLDO12), U101.24 (DVDD12), U101.48 (AVDD12)
/CAM2_3V3: C103.1, C104.1, C105.1, C106.1, C119.1, FB101.1, R103.1, R104.1, R106.1, U101.10 (DVDD33), U101.14 (DVDD33), U101.17 (VLDO33), U101.20 (DVDD33), U101.34 (DVDD33), U101.46 (DVDD33), U103.8 (VCC)
/CAM2_3V3A: C107.1, C108.1, C109.1, C110.1, FB101.2, U101.1 (AVDD33), U101.4 (AVDD33), U101.7 (AVDD33), U101.30 (AVDD33_USB), U101.40 (AVDD33_AU)
/CAM2_AVIN: C118.2, U101.8 (AVIN)
/CAM2_CVBS: C118.1, J101.1, R102.1, U102.1 (I/O1), U102.6 (I/O1)
/CAM2_DM: U10.5 (DM2-), U101.33 (USBDM)
/CAM2_DP: U10.6 (DP2+), U101.32 (USBDP)
/CAM2_GPIO4: D101.1 (K), R105.1, U101.19 (GPIO4/WP)
/CAM2_LED_A: D101.2 (A), R106.2
/CAM2_REXT: R101.1, U101.31 (REXT)
/CAM2_SCL: R103.2, U101.13 (GPIO2/SCL), U103.6 (SCL)
/CAM2_SDA: R104.2, U101.12 (GPIO3/SDA), U103.5 (SDA)
/CAM2_VCOML: C116.1, U101.41 (VCOML)
/CAM2_VCOMR: C117.1, U101.44 (VCOMR)
/CAM2_WP: R105.2, U103.7 (WP)
/CAM2_XI: C114.1, U101.27 (XTALI), Y101.1
/CAM2_XO: C115.1, U101.26 (XTALO), Y101.3
/CAPH_3V3: C31.1, C32.1, U10.9 (~RESET/CDP), U10.13 (VDD33)
/CAPH_P3_DM: J3.2, U10.3 (DM3-)
/CAPH_P3_DP: J3.3, U10.4 (DP3+)
/CAPH_XI: U10.16 (XI), Y10.1
/CAPH_XO: U10.15 (XO), Y10.3
/CAP_DM: J2.4, U10.10 (DMU-)
/CAP_DP: J2.3, U10.11 (DPU+)
GND: C1.2, C2.2, C3.2, C4.2, C5.2, C6.2, C7.2, C8.2, C9.2, C10.2, C11.2, C12.2, C13.2, C14.2, C15.2, C16.2, C17.2, C19.2, C30.2, C31.2, C32.2, C101.2, C102.2, C103.2, C104.2, C105.2, C106.2, C107.2, C108.2, C109.2, C110.2, C111.2, C112.2, C113.2, C114.2, C115.2, C116.2, C117.2, C119.2, J1.2, J2.5, J2.6, J3.4, J101.2, R1.2, R2.2, R101.2, R102.2, U1.2 (AVSS), U1.9 (AVSS), U1.11 (DVSS), U1.15 (AVSS), U1.21 (DVSS), U1.28 (AVSS), U1.29 (AVSS), U1.45 (AVSS), U1.47 (DVSS), U2.2 (GND), U3.4 (GND), U10.14 (GND), U101.2 (AVSS), U101.9 (AVSS), U101.11 (DVSS), U101.15 (AVSS), U101.21 (DVSS), U101.28 (AVSS), U101.29 (AVSS), U101.45 (AVSS), U101.47 (DVSS), U102.2 (GND), U103.4 (GND), Y1.2, Y1.4, Y10.2, Y10.4, Y101.2, Y101.4; also elsewhere on the board

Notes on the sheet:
CAPTURE MODULE: MacroSilicon MS2107 composite video (CVBS) -> USB 2.0 UVC. Reference: MS2107 datasheet + MS2106 eval board (BertoldVdb/ms-tools).
Car radio capture module rev 0.7 - two MS2107 composite video to USB (UVC) channels behind a CH334R hub, for two cameras; stacks on the USB module (J2 -> J29, hub 2 port 4). Generated by capture_gen.py.
